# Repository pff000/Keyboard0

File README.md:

# Keyboard0
Basic Keyboard PCB

- 64 key orthogonal keyboard with Kaihl low-profile switches.

- The switches are logically arranged n 8x8 matrix but physically in 5 1/2 rows.

- There is no brain in the PCB, just a 2x8 header.

USB keyboard with adafruit feather rp2040

- 8 column and 8 row gpio's connected directly to the keyboard matrix.

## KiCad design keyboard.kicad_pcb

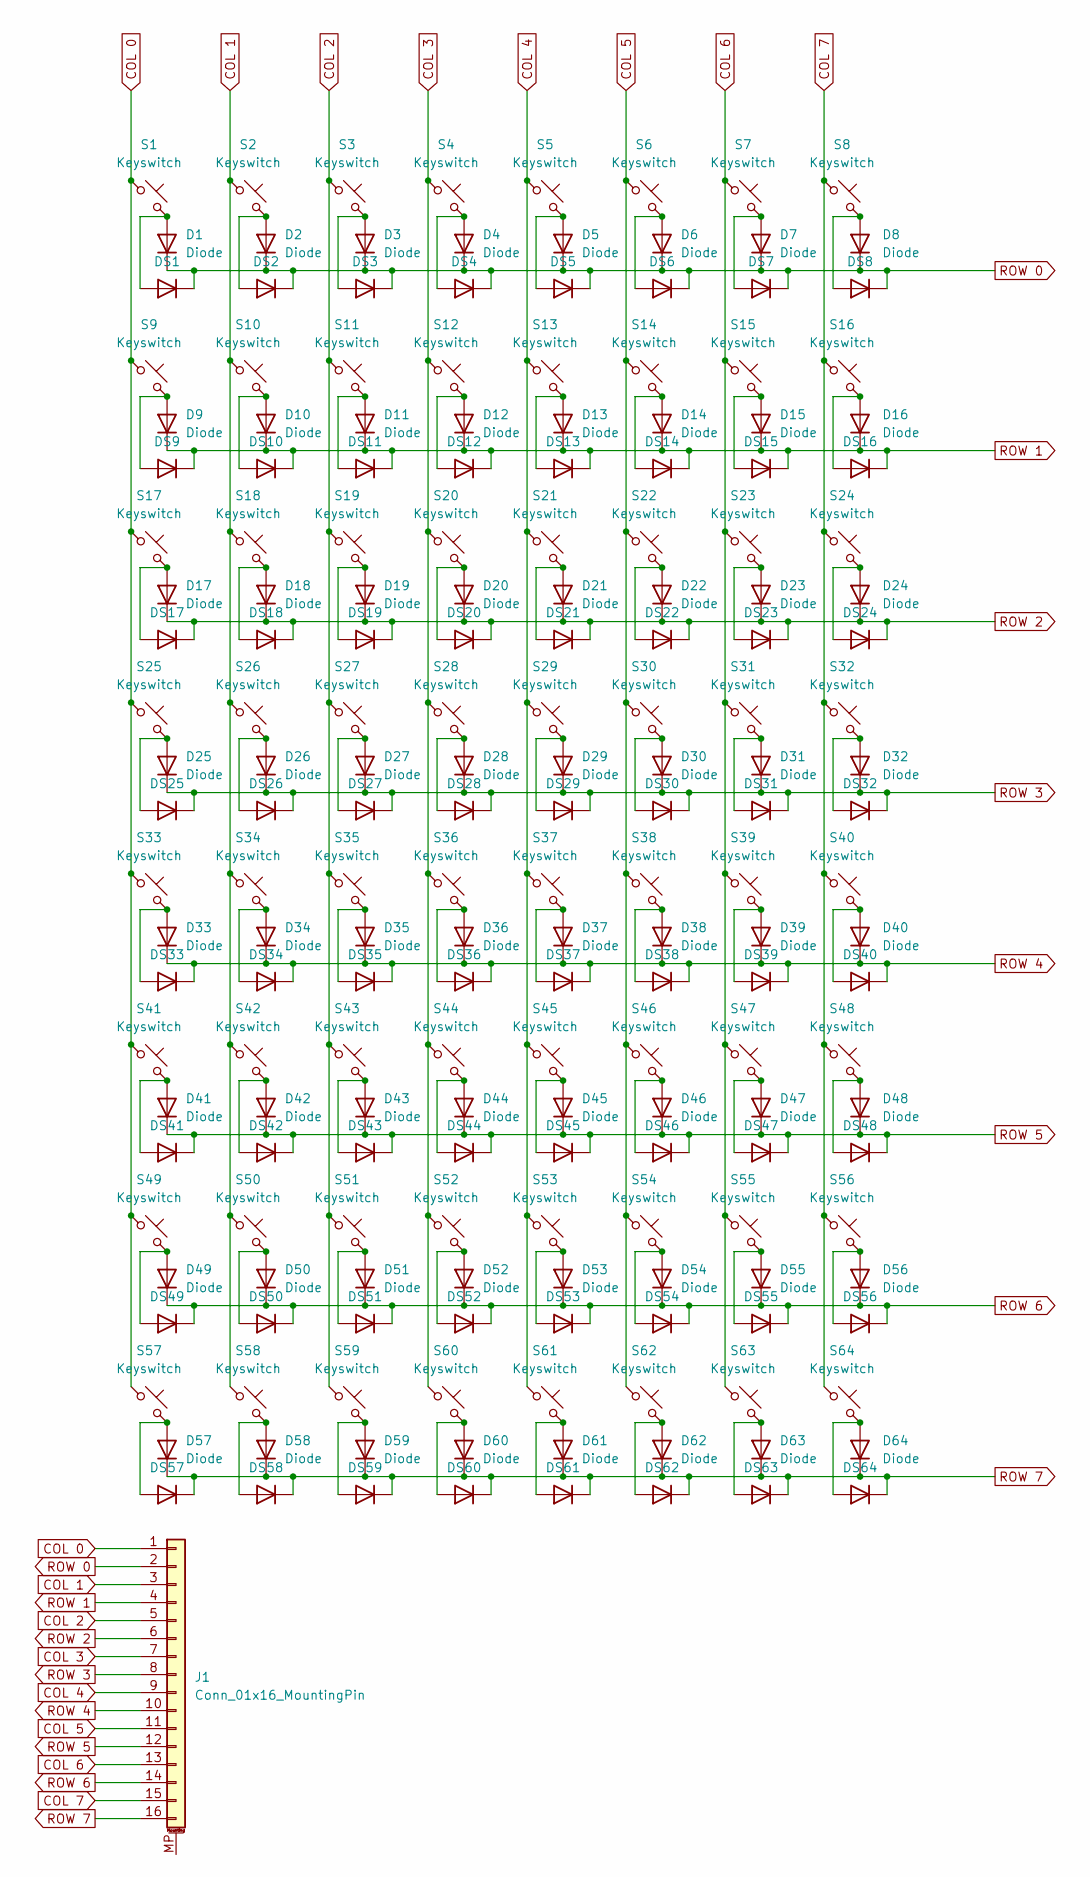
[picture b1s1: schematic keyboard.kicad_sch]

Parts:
D1, D2, D3, D4, D5, D6, D7, D8, D9, D10, D11, D12, D13, D14, D15, D16, D17, D18, D19, D20, D21, D22, D23, D24, D25, D26, D27, D28, D29, D30, D31, D32, D33, D34, D35, D36, D37, D38, D39, D40, D41, D42, D43, D44, D45, D46, D47, D48, D49, D50, D51, D52, D53, D54, D55, D56, D57, D58, D59, D60, D61, D62, D63, D64: Diode; Diode_DO-35
DS1, DS2, DS3, DS4, DS5, DS6, DS7, DS8, DS9, DS10, DS11, DS12, DS13, DS14, DS15, DS16, DS17, DS18, DS19, DS20, DS21, DS22, DS23, DS24, DS25, DS26, DS27, DS28, DS29, DS30, DS31, DS32, DS33, DS34, DS35, DS36, DS37, DS38, DS39, DS40, DS41, DS42, DS43, DS44, DS45, DS46, DS47, DS48, DS49, DS50, DS51, DS52, DS53, DS54, DS55, DS56, DS57, DS58, DS59, DS60, DS61, DS62, DS63, DS64: 1N4148W; D_SOD-123
J1: Conn_01x16_MountingPin; IDC-Header_2x08-1MP_P2.54mm_Latch_Vertical
S1, S2, S3, S4, S5, S6, S7, S8, S9, S10, S11, S12, S13, S14, S15, S16, S17, S18, S19, S20, S21, S22, S23, S24, S25, S26, S27, S28, S29, S30, S31, S32, S33, S34, S35, S36, S37, S38, S39, S40, S41, S42, S43, S44, S45, S46, S47, S48, S49, S50, S51, S52, S53, S54, S55, S56, S57, S58, S59, S60, S61, S62, S63, S64: Keyswitch; Choc_V1_1.00u

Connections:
COL 0: J1.1, S1.1, S9.1, S17.1, S25.1, S33.1, S41.1, S49.1, S57.1
COL 1: J1.3, S2.1, S10.1, S18.1, S26.1, S34.1, S42.1, S50.1, S58.1
COL 2: J1.5, S3.1, S11.1, S19.1, S27.1, S35.1, S43.1, S51.1, S59.1
COL 3: J1.7, S4.1, S12.1, S20.1, S28.1, S36.1, S44.1, S52.1, S60.1
COL 4: J1.9, S5.1, S13.1, S21.1, S29.1, S37.1, S45.1, S53.1, S61.1
COL 5: J1.11, S6.1, S14.1, S22.1, S30.1, S38.1, S46.1, S54.1, S62.1
COL 6: J1.13, S7.1, S15.1, S23.1, S31.1, S39.1, S47.1, S55.1, S63.1
COL 7: J1.15, S8.1, S16.1, S24.1, S32.1, S40.1, S48.1, S56.1, S64.1
unnamed: D1.2 (A), DS1.2 (A), S1.2
unnamed: D2.2 (A), DS2.2 (A), S2.2
unnamed: D3.2 (A), DS3.2 (A), S3.2
unnamed: D4.2 (A), DS4.2 (A), S4.2
unnamed: D5.2 (A), DS5.2 (A), S5.2
unnamed: D6.2 (A), DS6.2 (A), S6.2
unnamed: D7.2 (A), DS7.2 (A), S7.2
unnamed: D8.2 (A), DS8.2 (A), S8.2
unnamed: D9.2 (A), DS9.2 (A), S9.2
unnamed: D10.2 (A), DS10.2 (A), S10.2
unnamed: D11.2 (A), DS11.2 (A), S11.2
unnamed: D12.2 (A), DS12.2 (A), S12.2
unnamed: D13.2 (A), DS13.2 (A), S13.2
unnamed: D14.2 (A), DS14.2 (A), S14.2
unnamed: D15.2 (A), DS15.2 (A), S15.2
unnamed: D16.2 (A), DS16.2 (A), S16.2
unnamed: D17.2 (A), DS17.2 (A), S17.2
unnamed: D18.2 (A), DS18.2 (A), S18.2
unnamed: D19.2 (A), DS19.2 (A), S19.2
unnamed: D20.2 (A), DS20.2 (A), S20.2
unnamed: D21.2 (A), DS21.2 (A), S21.2
unnamed: D22.2 (A), DS22.2 (A), S22.2
unnamed: D23.2 (A), DS23.2 (A), S23.2
unnamed: D24.2 (A), DS24.2 (A), S24.2
unnamed: D25.2 (A), DS25.2 (A), S25.2
unnamed: D26.2 (A), DS26.2 (A), S26.2
unnamed: D27.2 (A), DS27.2 (A), S27.2
unnamed: D28.2 (A), DS28.2 (A), S28.2
unnamed: D29.2 (A), DS29.2 (A), S29.2
unnamed: D30.2 (A), DS30.2 (A), S30.2
unnamed: D31.2 (A), DS31.2 (A), S31.2
unnamed: D32.2 (A), DS32.2 (A), S32.2
unnamed: D33.2 (A), DS33.2 (A), S33.2
unnamed: D34.2 (A), DS34.2 (A), S34.2
unnamed: D35.2 (A), DS35.2 (A), S35.2
unnamed: D36.2 (A), DS36.2 (A), S36.2
unnamed: D37.2 (A), DS37.2 (A), S37.2
unnamed: D38.2 (A), DS38.2 (A), S38.2
unnamed: D39.2 (A), DS39.2 (A), S39.2
unnamed: D40.2 (A), DS40.2 (A), S40.2
unnamed: D41.2 (A), DS41.2 (A), S41.2
unnamed: D42.2 (A), DS42.2 (A), S42.2
unnamed: D43.2 (A), DS43.2 (A), S43.2
unnamed: D44.2 (A), DS44.2 (A), S44.2
unnamed: D45.2 (A), DS45.2 (A), S45.2
unnamed: D46.2 (A), DS46.2 (A), S46.2
unnamed: D47.2 (A), DS47.2 (A), S47.2
unnamed: D48.2 (A), DS48.2 (A), S48.2
unnamed: D49.2 (A), DS49.2 (A), S49.2
unnamed: D50.2 (A), DS50.2 (A), S50.2
unnamed: D51.2 (A), DS51.2 (A), S51.2
unnamed: D52.2 (A), DS52.2 (A), S52.2
unnamed: D53.2 (A), DS53.2 (A), S53.2
unnamed: D54.2 (A), DS54.2 (A), S54.2
unnamed: D55.2 (A), DS55.2 (A), S55.2
unnamed: D56.2 (A), DS56.2 (A), S56.2
unnamed: D57.2 (A), DS57.2 (A), S57.2
unnamed: D58.2 (A), DS58.2 (A), S58.2
unnamed: D59.2 (A), DS59.2 (A), S59.2
unnamed: D60.2 (A), DS60.2 (A), S60.2
unnamed: D61.2 (A), DS61.2 (A), S61.2
unnamed: D62.2 (A), DS62.2 (A), S62.2
unnamed: D63.2 (A), DS63.2 (A), S63.2
unnamed: D64.2 (A), DS64.2 (A), S64.2
ROW 0: D1.1 (K), D2.1 (K), D3.1 (K), D4.1 (K), D5.1 (K), D6.1 (K), D7.1 (K), D8.1 (K), DS1.1 (K), DS2.1 (K), DS3.1 (K), DS4.1 (K), DS5.1 (K), DS6.1 (K), DS7.1 (K), DS8.1 (K), J1.2
ROW 1: D9.1 (K), D10.1 (K), D11.1 (K), D12.1 (K), D13.1 (K), D14.1 (K), D15.1 (K), D16.1 (K), DS9.1 (K), DS10.1 (K), DS11.1 (K), DS12.1 (K), DS13.1 (K), DS14.1 (K), DS15.1 (K), DS16.1 (K), J1.4
ROW 2: D17.1 (K), D18.1 (K), D19.1 (K), D20.1 (K), D21.1 (K), D22.1 (K), D23.1 (K), D24.1 (K), DS17.1 (K), DS18.1 (K), DS19.1 (K), DS20.1 (K), DS21.1 (K), DS22.1 (K), DS23.1 (K), DS24.1 (K), J1.6
ROW 3: D25.1 (K), D26.1 (K), D27.1 (K), D28.1 (K), D29.1 (K), D30.1 (K), D31.1 (K), D32.1 (K), DS25.1 (K), DS26.1 (K), DS27.1 (K), DS28.1 (K), DS29.1 (K), DS30.1 (K), DS31.1 (K), DS32.1 (K), J1.8
ROW 4: D33.1 (K), D34.1 (K), D35.1 (K), D36.1 (K), D37.1 (K), D38.1 (K), D39.1 (K), D40.1 (K), DS33.1 (K), DS34.1 (K), DS35.1 (K), DS36.1 (K), DS37.1 (K), DS38.1 (K), DS39.1 (K), DS40.1 (K), J1.10
ROW 5: D41.1 (K), D42.1 (K), D43.1 (K), D44.1 (K), D45.1 (K), D46.1 (K), D47.1 (K), D48.1 (K), DS41.1 (K), DS42.1 (K), DS43.1 (K), DS44.1 (K), DS45.1 (K), DS46.1 (K), DS47.1 (K), DS48.1 (K), J1.12
ROW 6: D49.1 (K), D50.1 (K), D51.1 (K), D52.1 (K), D53.1 (K), D54.1 (K), D55.1 (K), D56.1 (K), DS49.1 (K), DS50.1 (K), DS51.1 (K), DS52.1 (K), DS53.1 (K), DS54.1 (K), DS55.1 (K), DS56.1 (K), J1.14
ROW 7: D57.1 (K), D58.1 (K), D59.1 (K), D60.1 (K), D61.1 (K), D62.1 (K), D63.1 (K), D64.1 (K), DS57.1 (K), DS58.1 (K), DS59.1 (K), DS60.1 (K), DS61.1 (K), DS62.1 (K), DS63.1 (K), DS64.1 (K), J1.16

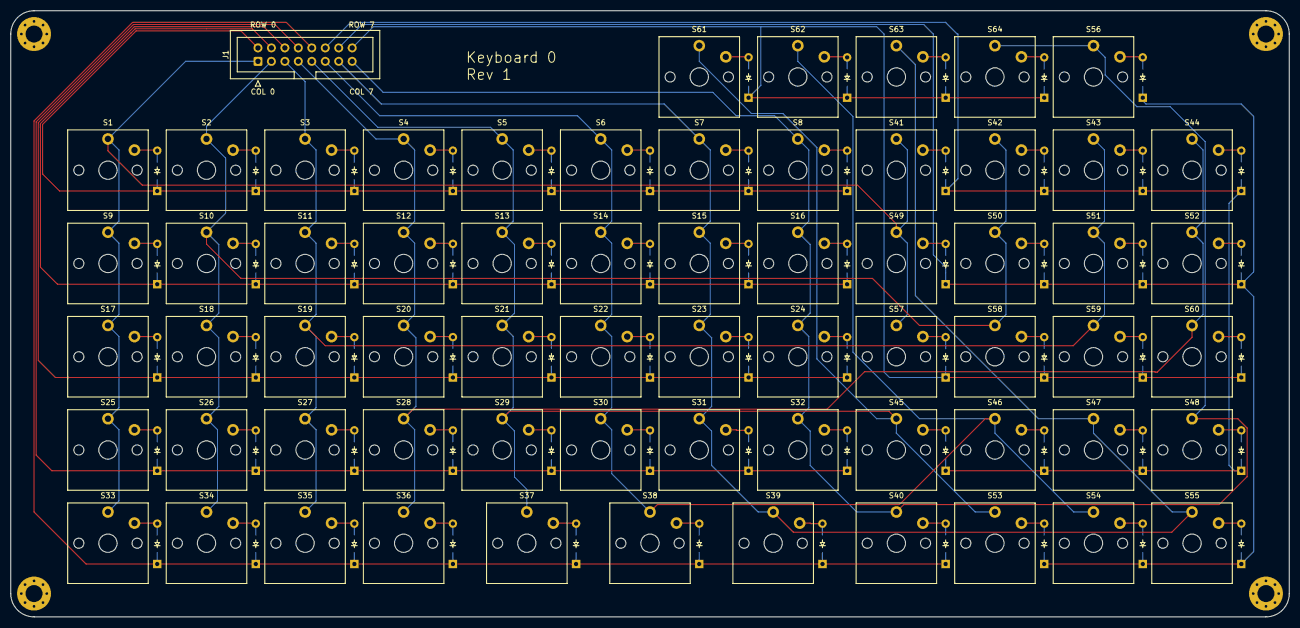
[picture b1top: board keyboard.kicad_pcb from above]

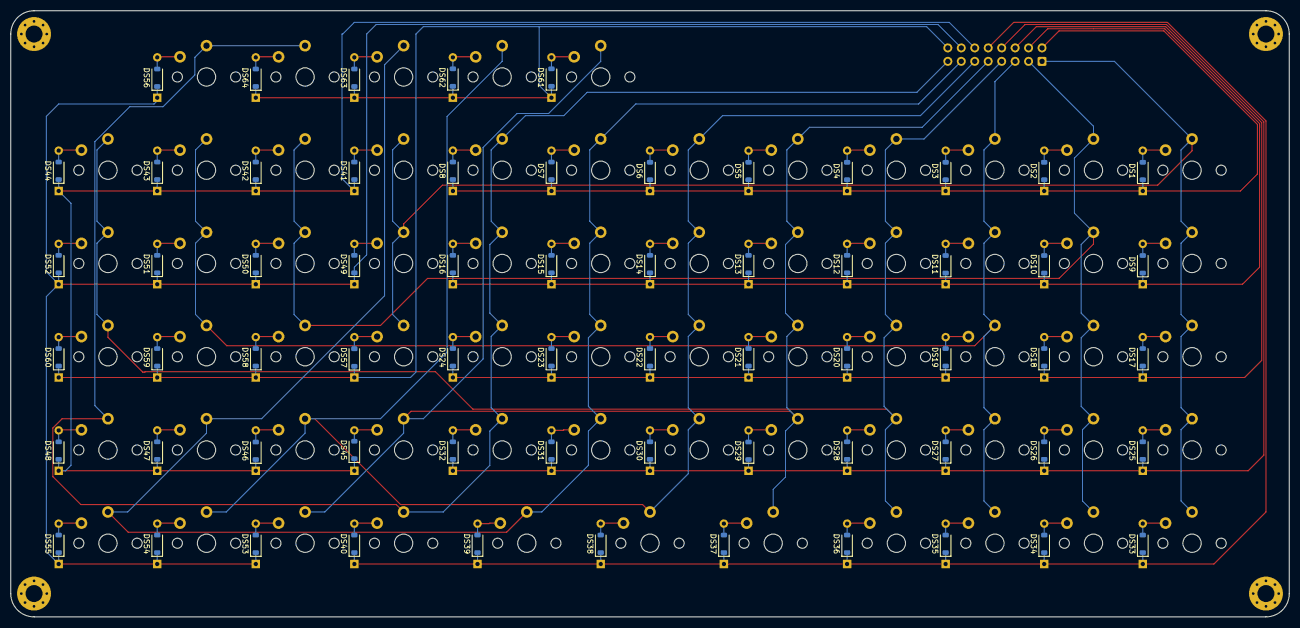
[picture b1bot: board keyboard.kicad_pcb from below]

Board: 2 copper layers, 241.3 x 114.4 mm, 193 parts (64 on the bottom side), 80 nets.

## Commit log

2025-09-22 copy files
2025-10-02 feather board and firmware import
2025-10-02 alignment picture
